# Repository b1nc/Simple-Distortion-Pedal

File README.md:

# Simple-Distortion-Pedal
A simple guitar distortion pedal.

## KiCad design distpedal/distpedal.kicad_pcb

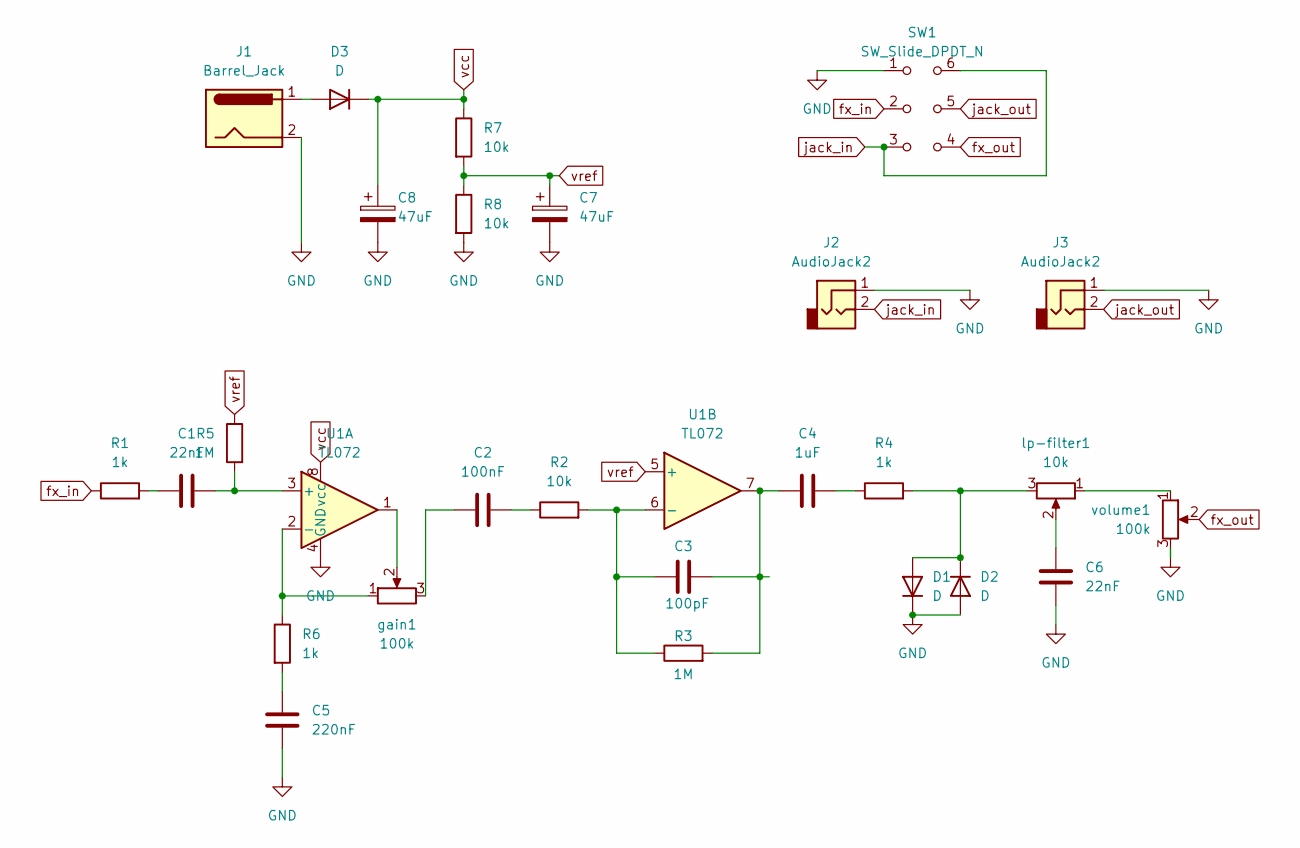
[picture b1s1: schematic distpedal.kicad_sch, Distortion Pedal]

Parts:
C1, C6: 22nF; C_Rect_L7.2mm_W2.5mm_P5.00mm_FKS2_FKP2_MKS2_MKP2
C2: 100nF; C_Rect_L7.2mm_W2.5mm_P5.00mm_FKS2_FKP2_MKS2_MKP2
C3: 100pF; C_Rect_L7.2mm_W4.5mm_P5.00mm_FKS2_FKP2_MKS2_MKP2
C4: 1uF; C_Rect_L7.2mm_W5.5mm_P5.00mm_FKS2_FKP2_MKS2_MKP2
C5: 220nF; C_Rect_L7.2mm_W3.5mm_P5.00mm_FKS2_FKP2_MKS2_MKP2
C7, C8: 47uF; CP_Radial_D6.3mm_P2.50mm
D1, D2: D; D_DO-35_SOD27_P7.62mm_Horizontal
D3: D; D_DO-41_SOD81_P7.62mm_Horizontal
J1: Barrel_Jack; BarrelJack_Horizontal
J2, J3: AudioJack2; 6.35_stereo_phone_jack_tayda
R1, R4, R6: 1k; R_Axial_DIN0414_L11.9mm_D4.5mm_P15.24mm_Horizontal
R2, R7, R8: 10k; R_Axial_DIN0414_L11.9mm_D4.5mm_P15.24mm_Horizontal
R3, R5: 1M; R_Axial_DIN0207_L6.3mm_D2.5mm_P10.16mm_Horizontal
SW1: SW_Slide_DPDT_N; DPDT_1MD1T1B1M1QE
U1: TL072; P8
gain1: 100k; Rotary_Potentiometer_RV9312NO-OS15A00-B10K-060
lp-filter1: 10k; Rotary_Potentiometer_RV9312NO-OS15A00-B10K-060
volume1: 100k; Rotary_Potentiometer_RV9312NO-OS15A00-B10K-060

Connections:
GND: C5.2, C6.2, C7.2, C8.2, D1.1 (K), D2.2 (A), J1.2, J2.1, J3.1, R8.2, SW1.1 (A), U1.4 (GND), volume1.3
unnamed: C1.1, R1.2
unnamed: C2.1, gain1.3
unnamed: C2.2, R2.1
unnamed: C3.2, C4.1, R3.2, U1.7
unnamed: C4.2, R4.1
unnamed: C5.1, R6.2
unnamed: C6.1, lp-filter1.2
unnamed: D1.2 (A), D2.1 (K), R4.2, lp-filter1.3
unnamed: D3.2 (A), J1.1
unnamed: U1.1, gain1.2
unnamed: C1.2, R5.2, U1.3 (+)
unnamed: R6.1, U1.2 (-), gain1.1
unnamed: C3.1, R2.2, R3.1, U1.6 (-)
unnamed: lp-filter1.1, volume1.1
fx_in: R1.1, SW1.2 (B)
fx_out: SW1.4 (A), volume1.2
jack_in: J2.2, SW1.3 (C), SW1.6 (C)
jack_out: J3.2, SW1.5 (B)
vcc: C8.1, D3.1 (K), R7.1, U1.8 (vcc)
vref: C7.1, R5.1, R7.2, R8.1, U1.5 (+)

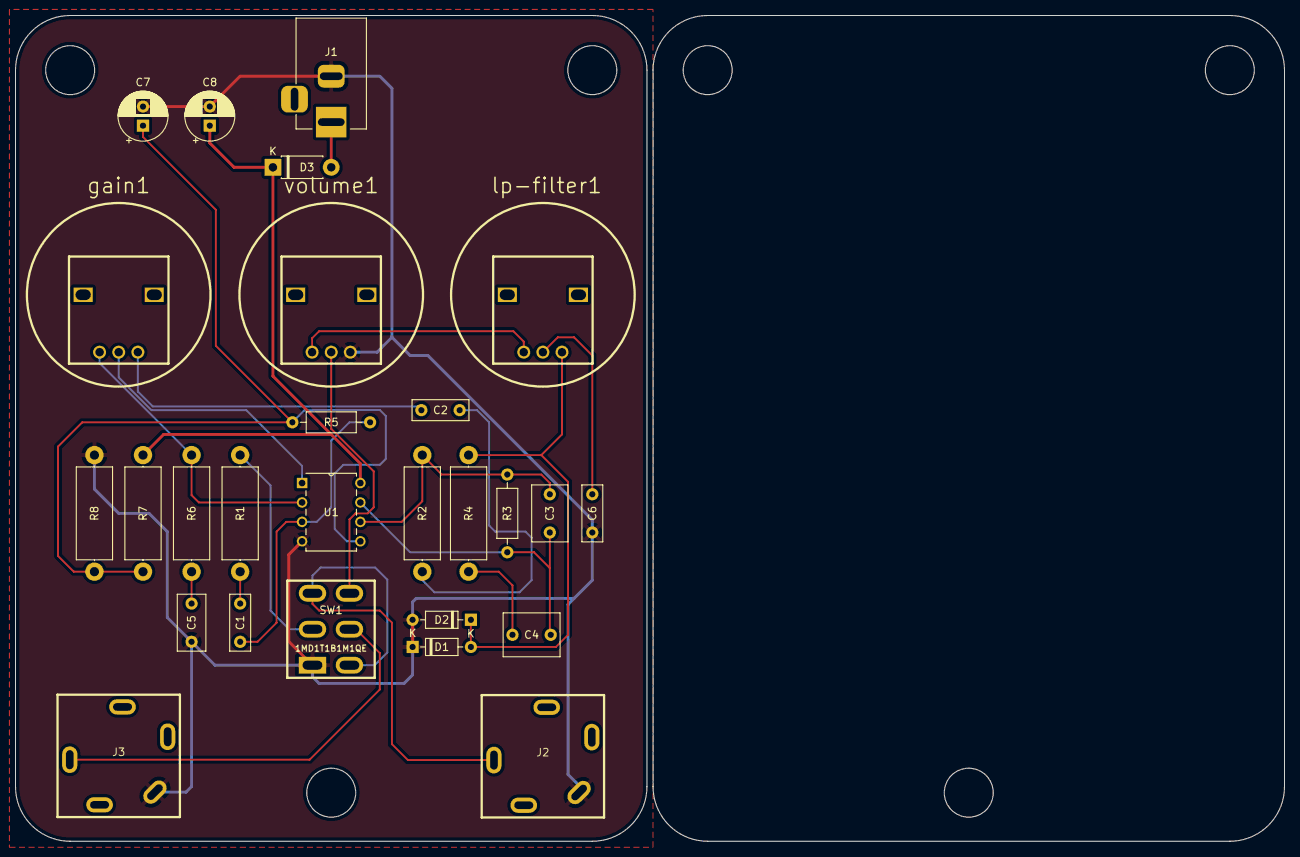
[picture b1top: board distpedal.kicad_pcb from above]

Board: 2 copper layers, 165.9 x 108.0 mm, 27 parts (0 on the bottom side), 21 nets.

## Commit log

2024-11-08 Initial
    Added all necessary files. May contain missing footprints, will add when issues arise.
